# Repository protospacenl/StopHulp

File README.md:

# StopHulp
Milling emergency bracelet

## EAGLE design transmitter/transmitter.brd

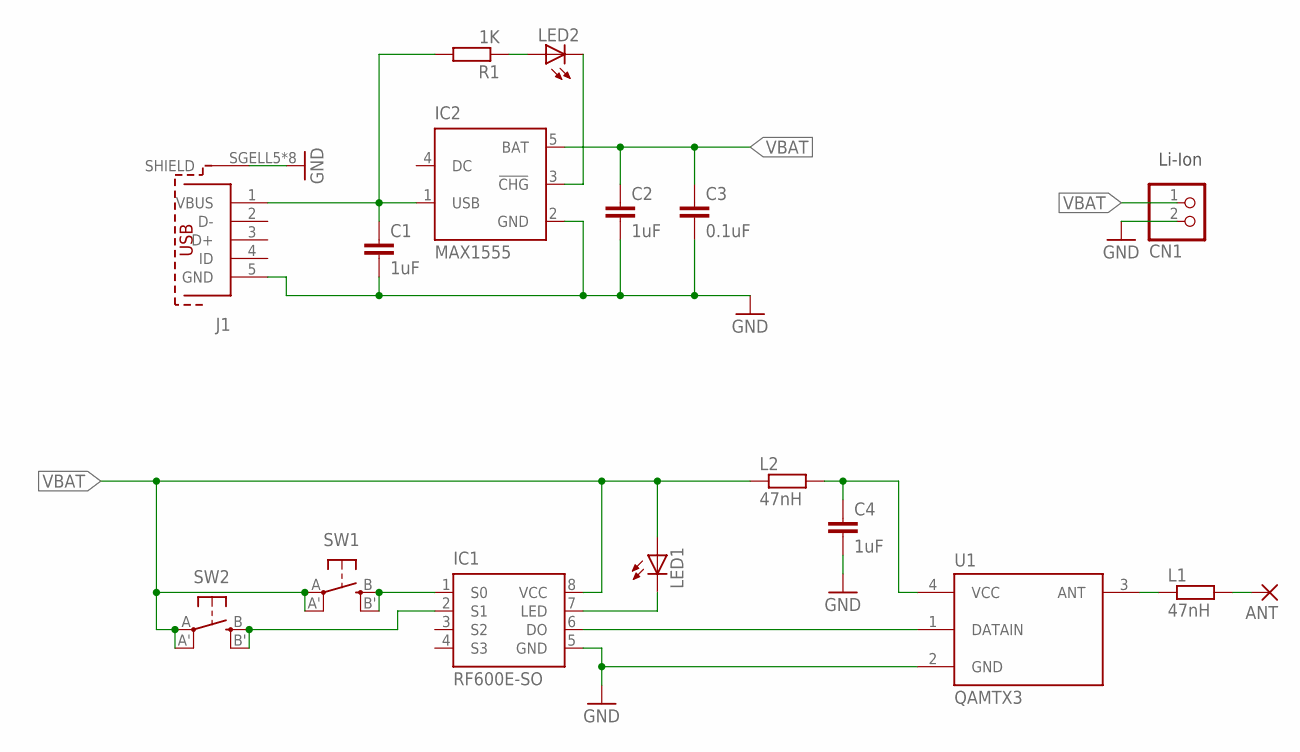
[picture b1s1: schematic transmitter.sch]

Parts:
ANT: SMD2; SMD1,27-2,54
C1, C2, C4: 1uF; C0603K
C3: 0.1uF; C0603K
CN1: JST_2PIN-SMT-RA; JST-PH-2-SMT-RA
IC1: RF600E-SO; SO-08
IC2: MAX1555; SOT23-5L
J1: 629105150921
L1, L2: 47nH; R0603
LED1, LED2: LEDCHIP-LED0805; CHIP-LED0805
R1: 1K; R0603
SW1, SW2: SPST_TACT-EVQQ2; EVQ-Q2
U1: QAMTX3; QAM-TX3

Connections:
ANT: L1.1, U1.3 (ANT)
DATAIN: IC1.6 (DO), U1.1 (DATAIN)
GND: C1.2, C2.2, C3.2, C4.2, CN1.2 (1), IC1.5 (GND), IC2.2 (GND), J1.5 (GND), J1.SGELL5 (SHIELD), J1.SHELL (SHIELD), J1.SHELL1 (SHIELD), J1.SHELL2 (SHIELD), J1.SHELL3 (SHIELD), J1.SHELL4 (SHIELD), J1.SHELL6 (SHIELD), J1.SHELL7 (SHIELD), U1.2 (GND)
unnamed: IC1.1 (S0), SW1.B (S), SW1.B' (S1)
unnamed: IC1.2 (S1), SW2.B (S), SW2.B' (S1)
unnamed: C4.1, L2.2, U1.4 (VCC)
unnamed: IC2.3 (!CHG), LED2.C
unnamed: IC1.7 (LED), LED1.C
unnamed: LED2.A, R1.1
unnamed: ANT.1, L1.2
VBAT: C2.1, C3.1, CN1.1 (2), IC1.8 (VCC), IC2.5 (BAT), L2.1, LED1.A, SW1.A, SW1.A' (P1), SW2.A, SW2.A' (P1)
VUSB: C1.1, IC2.1 (USB), J1.1 (VBUS), R1.2

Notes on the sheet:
Li-Ion

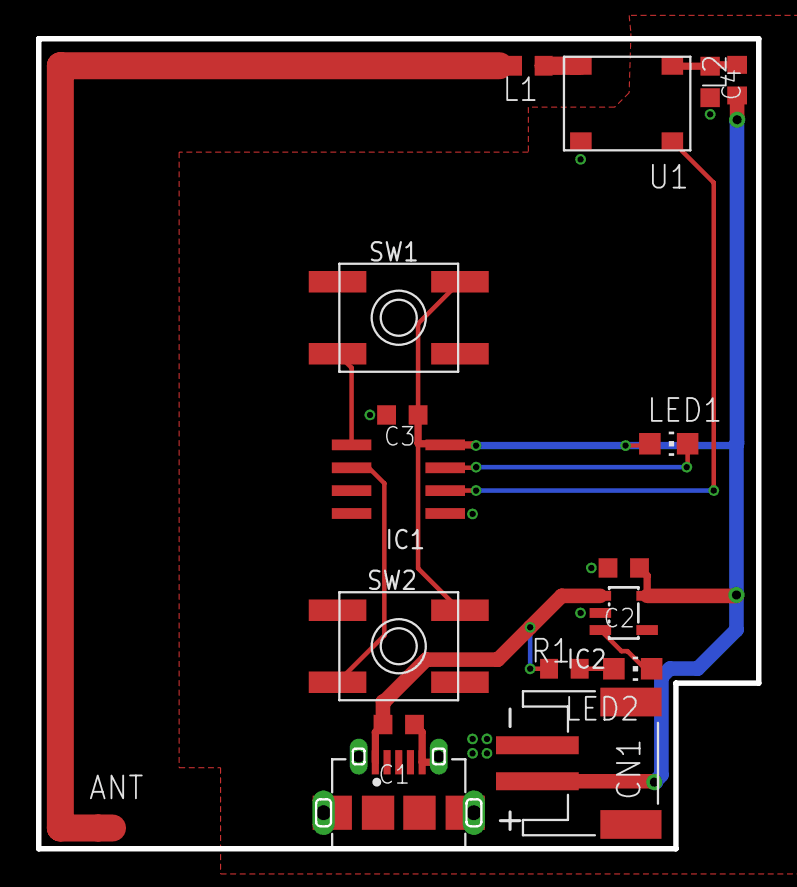
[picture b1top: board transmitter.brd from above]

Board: 2 copper layers, 40.0 x 45.0 mm, 17 parts (0 on the bottom side), 12 nets.

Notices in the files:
parts and their libraries:
InputOutputIO: Copyright: Würth Elektronik
